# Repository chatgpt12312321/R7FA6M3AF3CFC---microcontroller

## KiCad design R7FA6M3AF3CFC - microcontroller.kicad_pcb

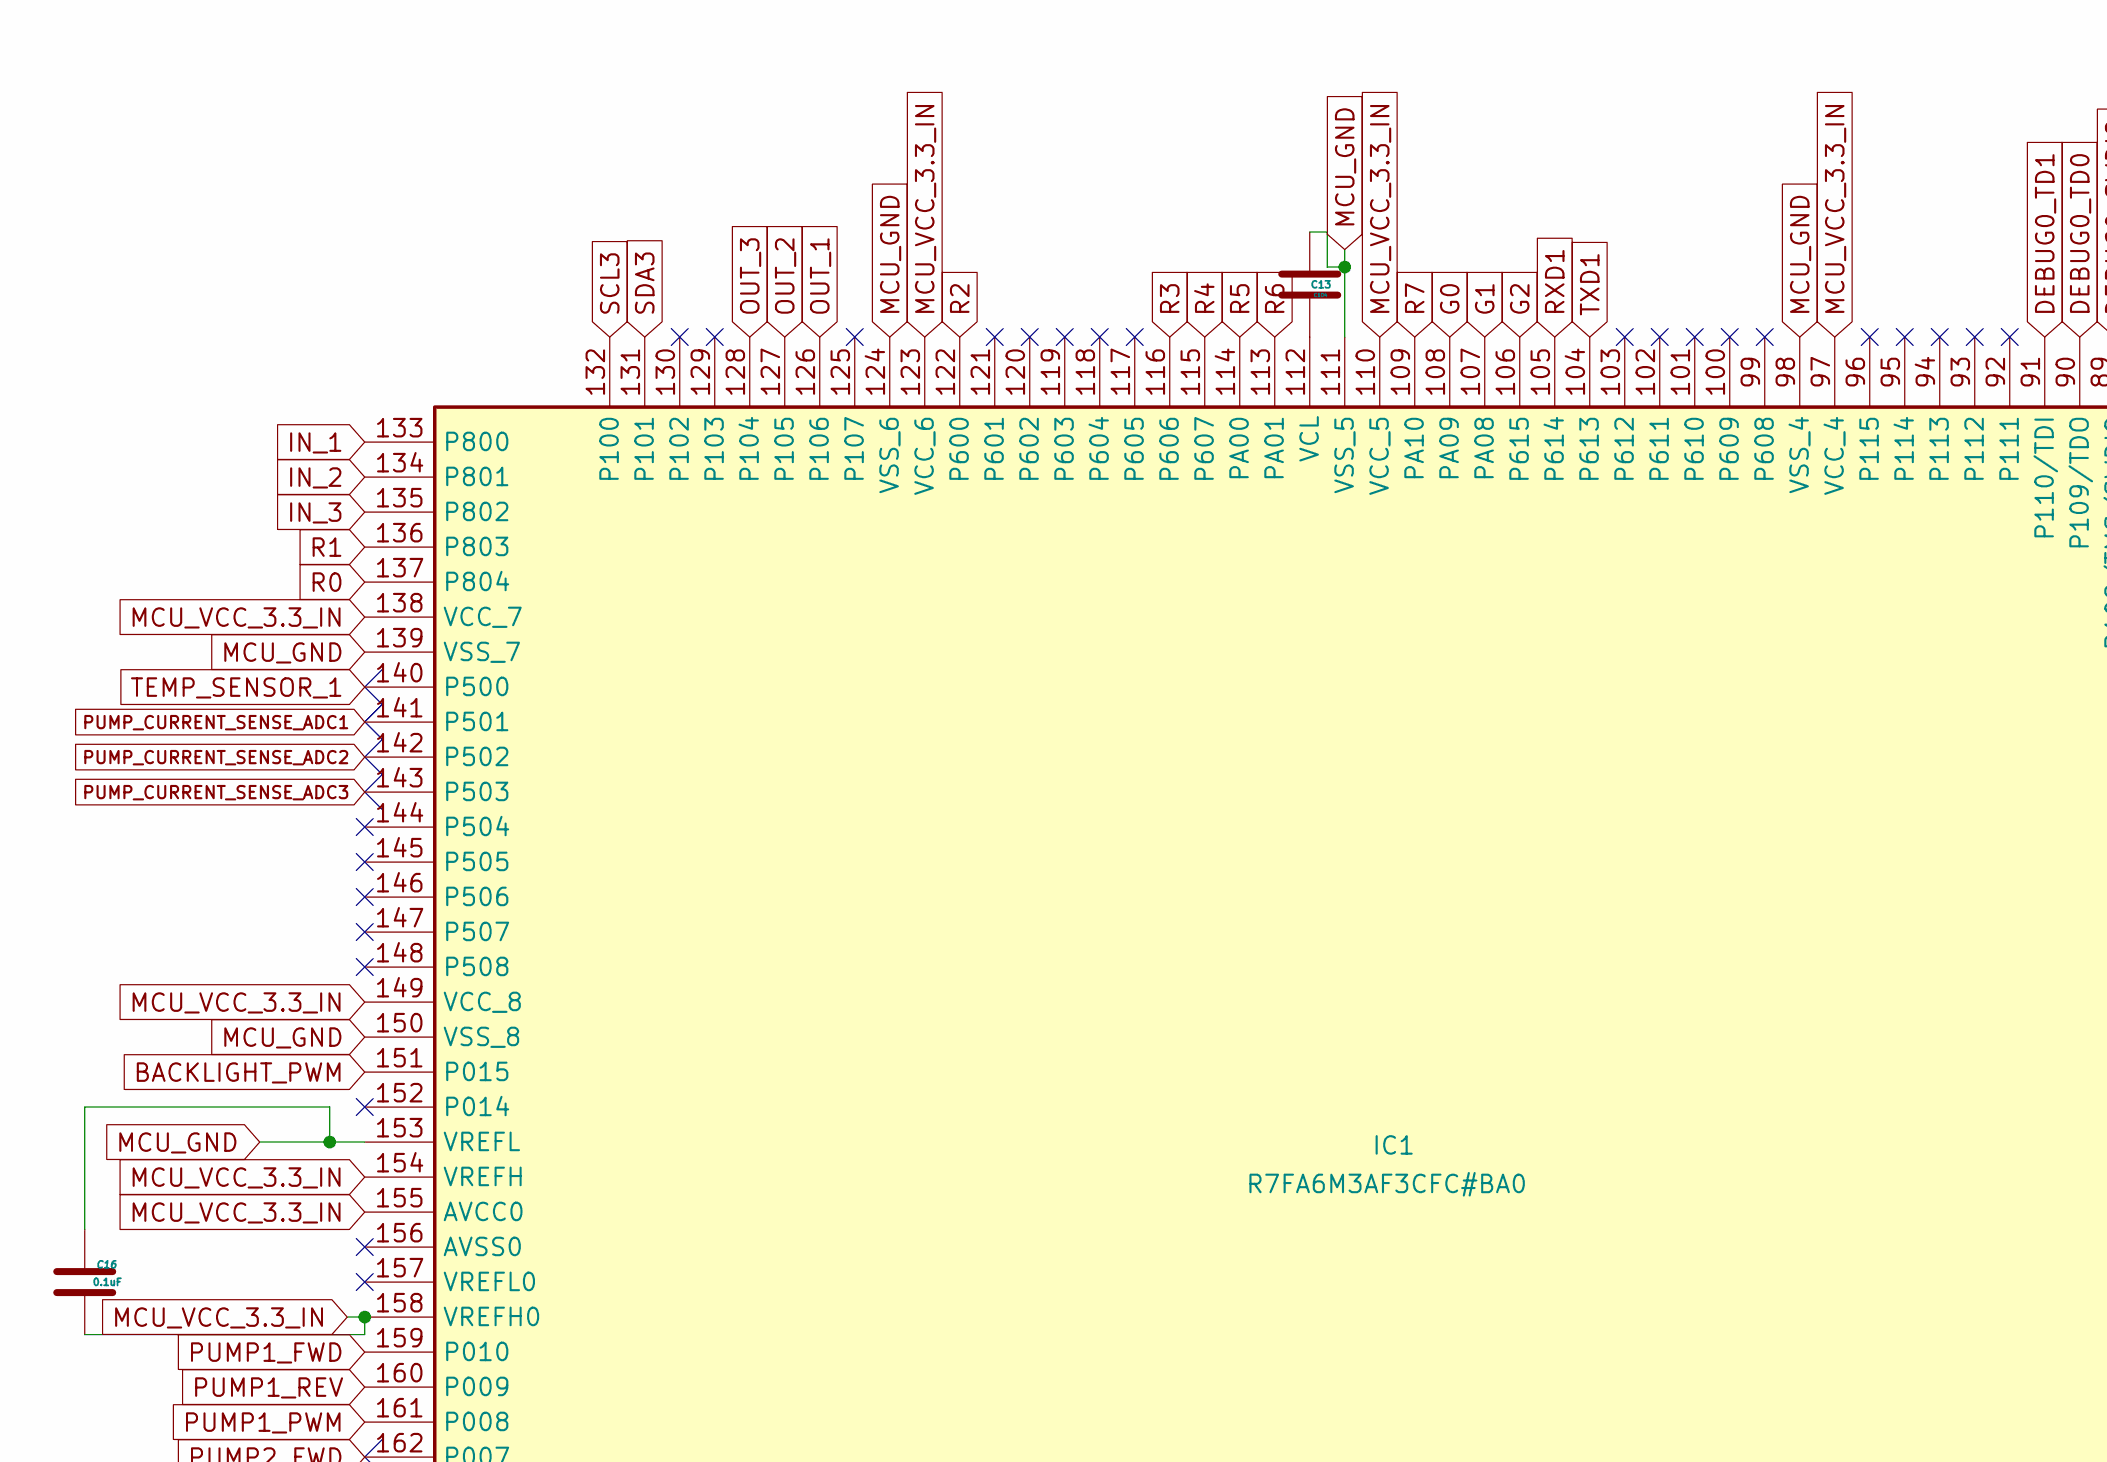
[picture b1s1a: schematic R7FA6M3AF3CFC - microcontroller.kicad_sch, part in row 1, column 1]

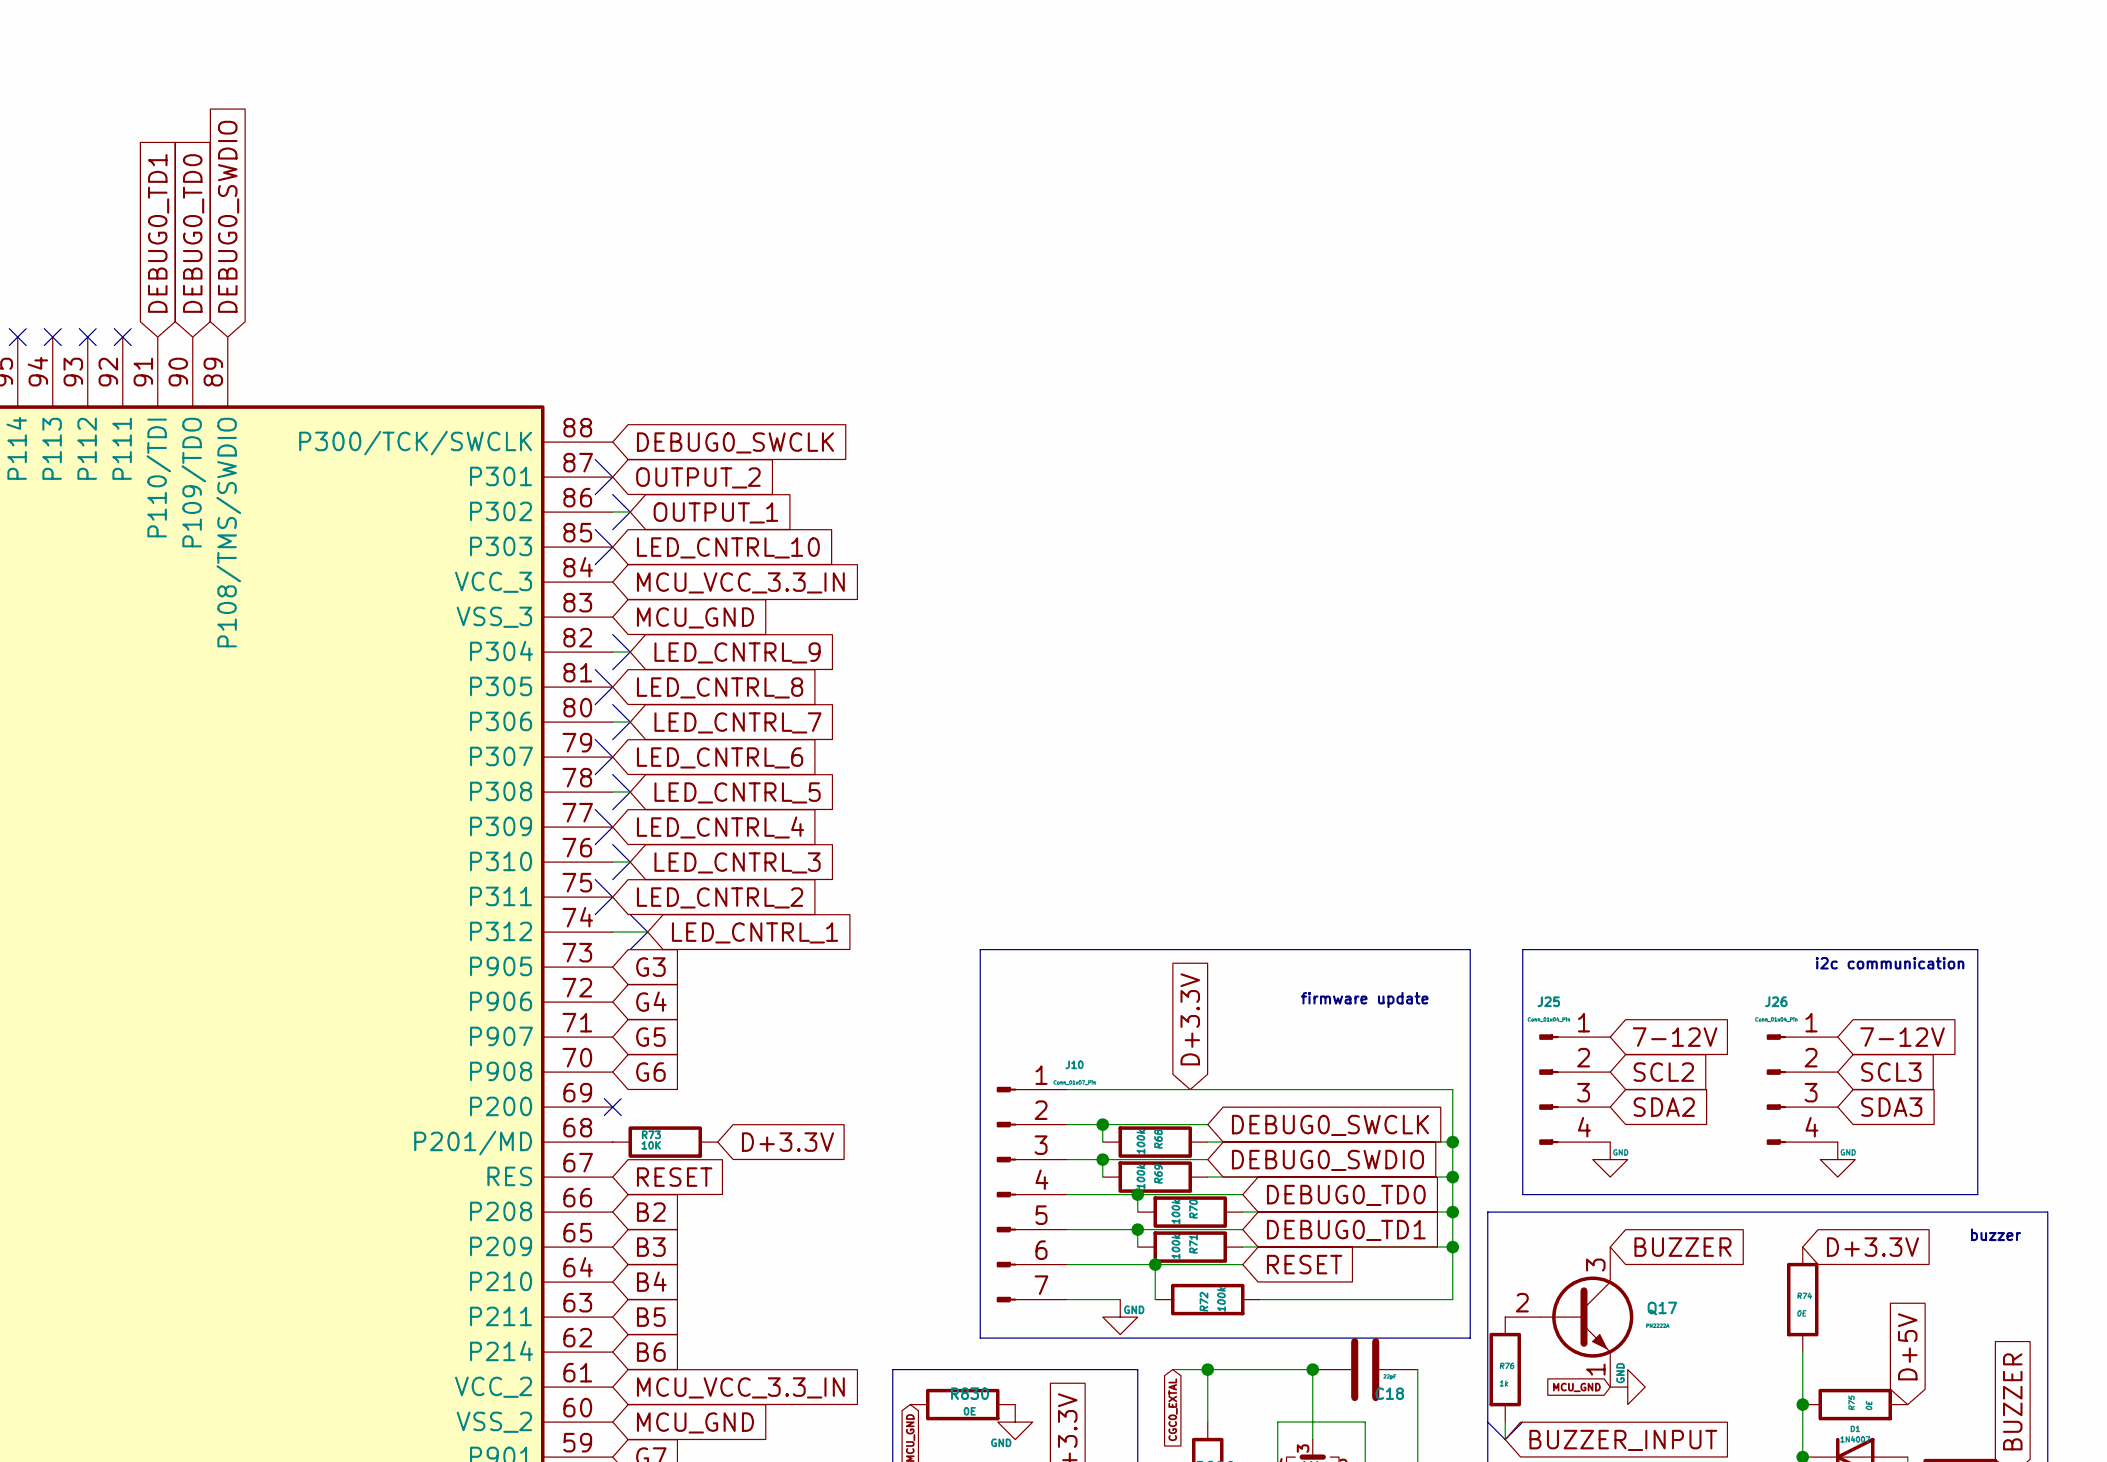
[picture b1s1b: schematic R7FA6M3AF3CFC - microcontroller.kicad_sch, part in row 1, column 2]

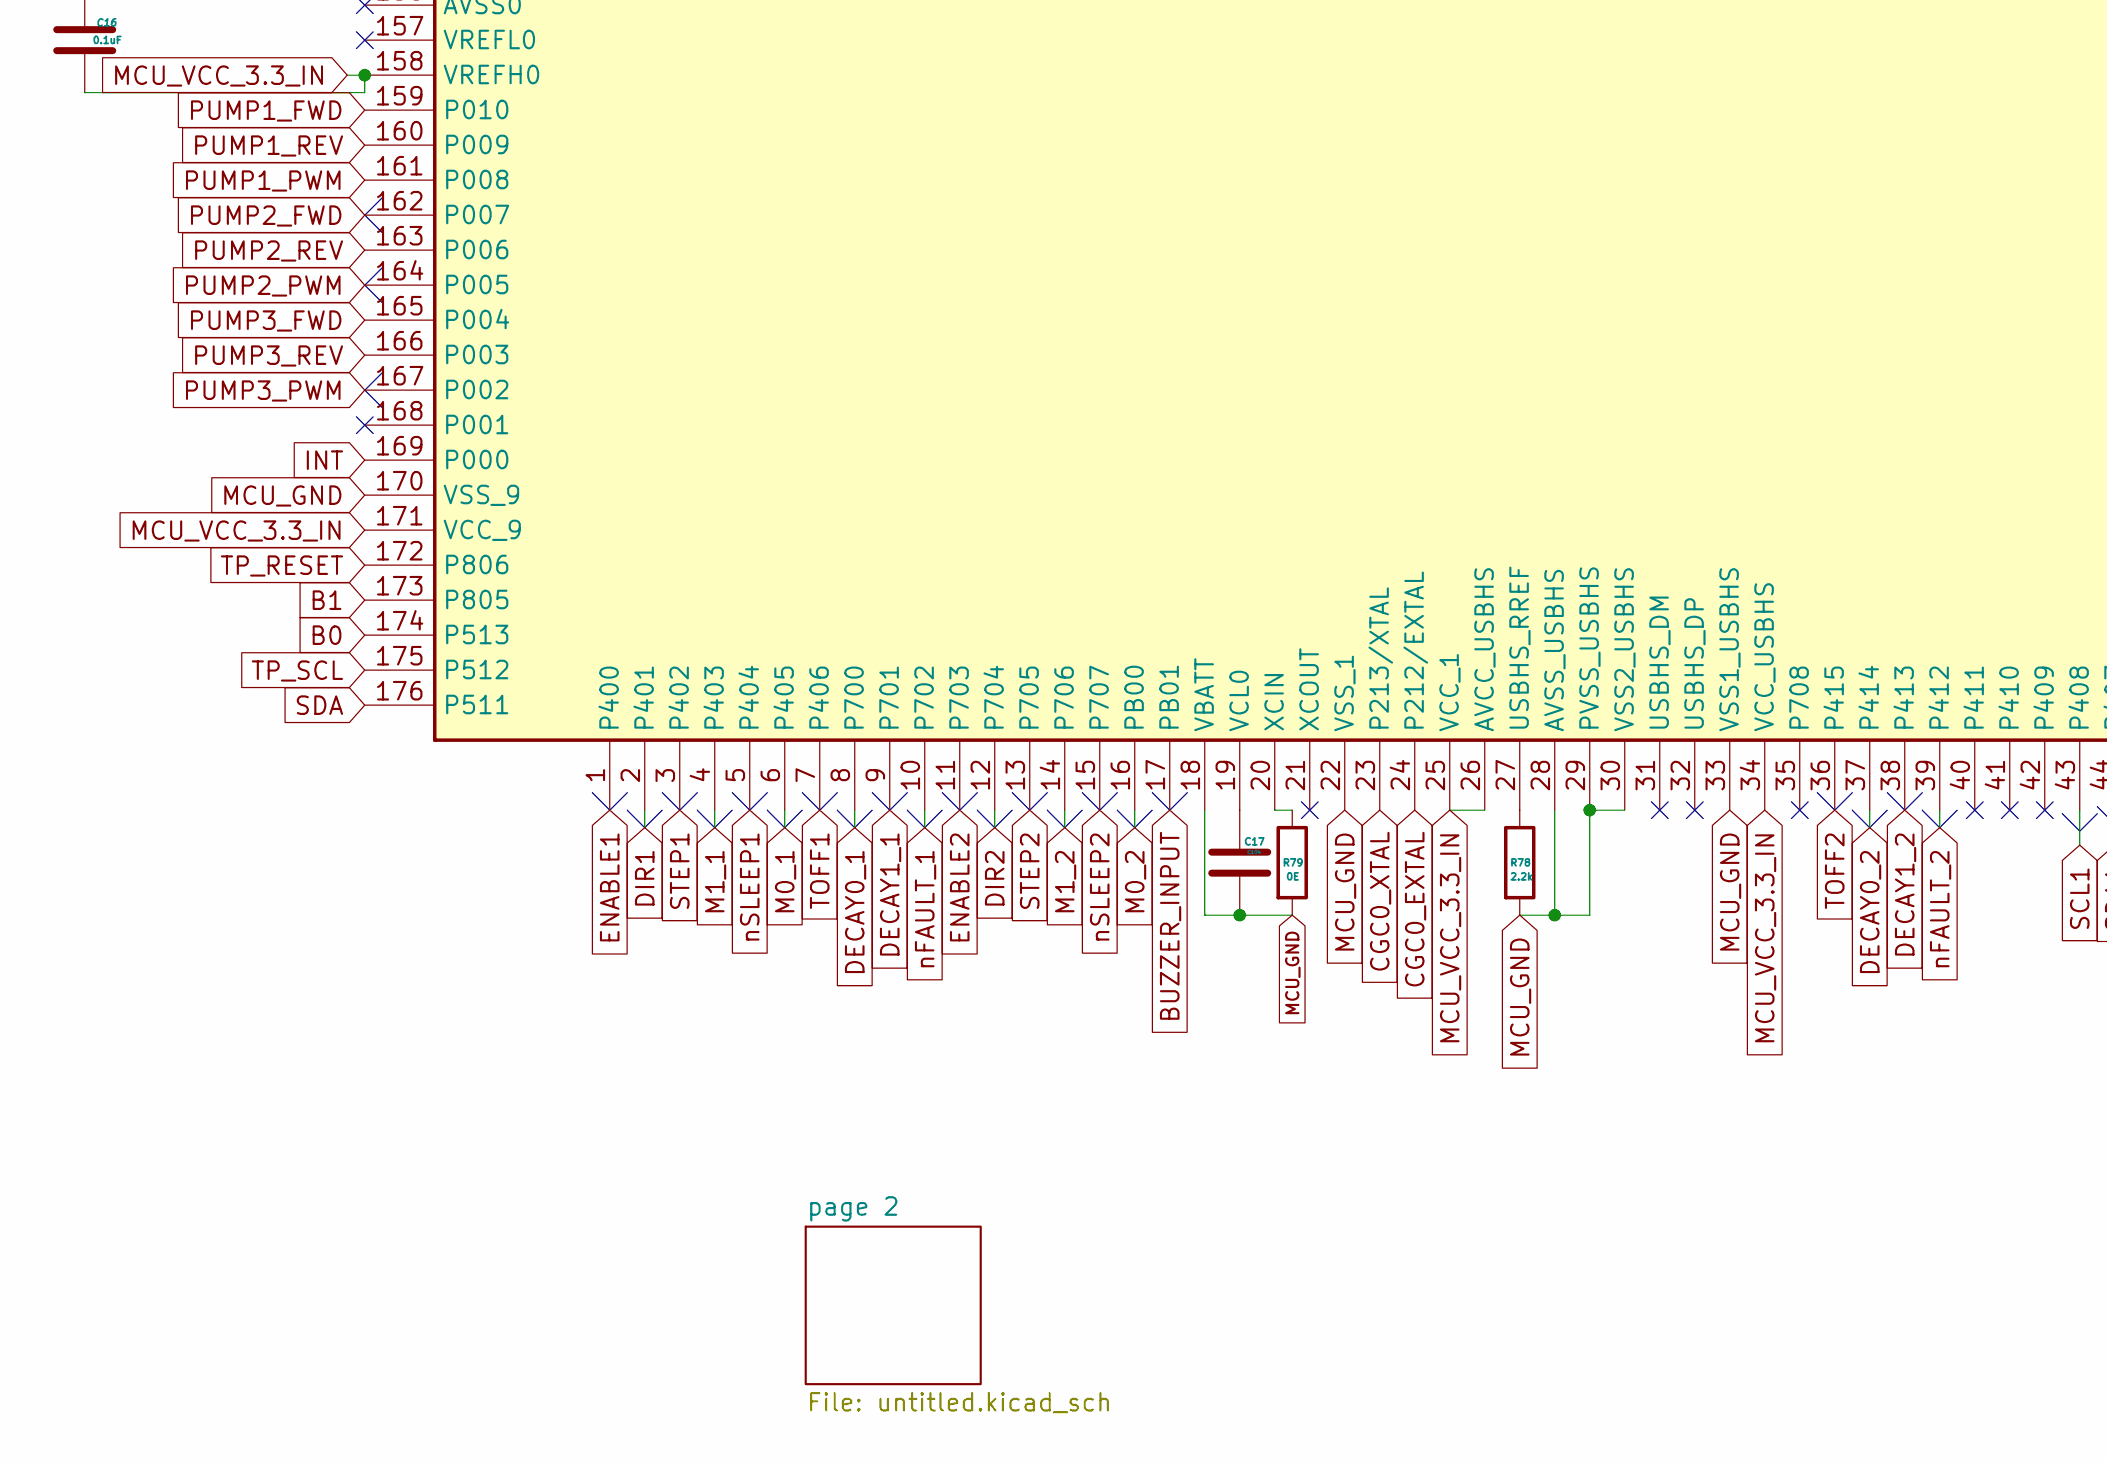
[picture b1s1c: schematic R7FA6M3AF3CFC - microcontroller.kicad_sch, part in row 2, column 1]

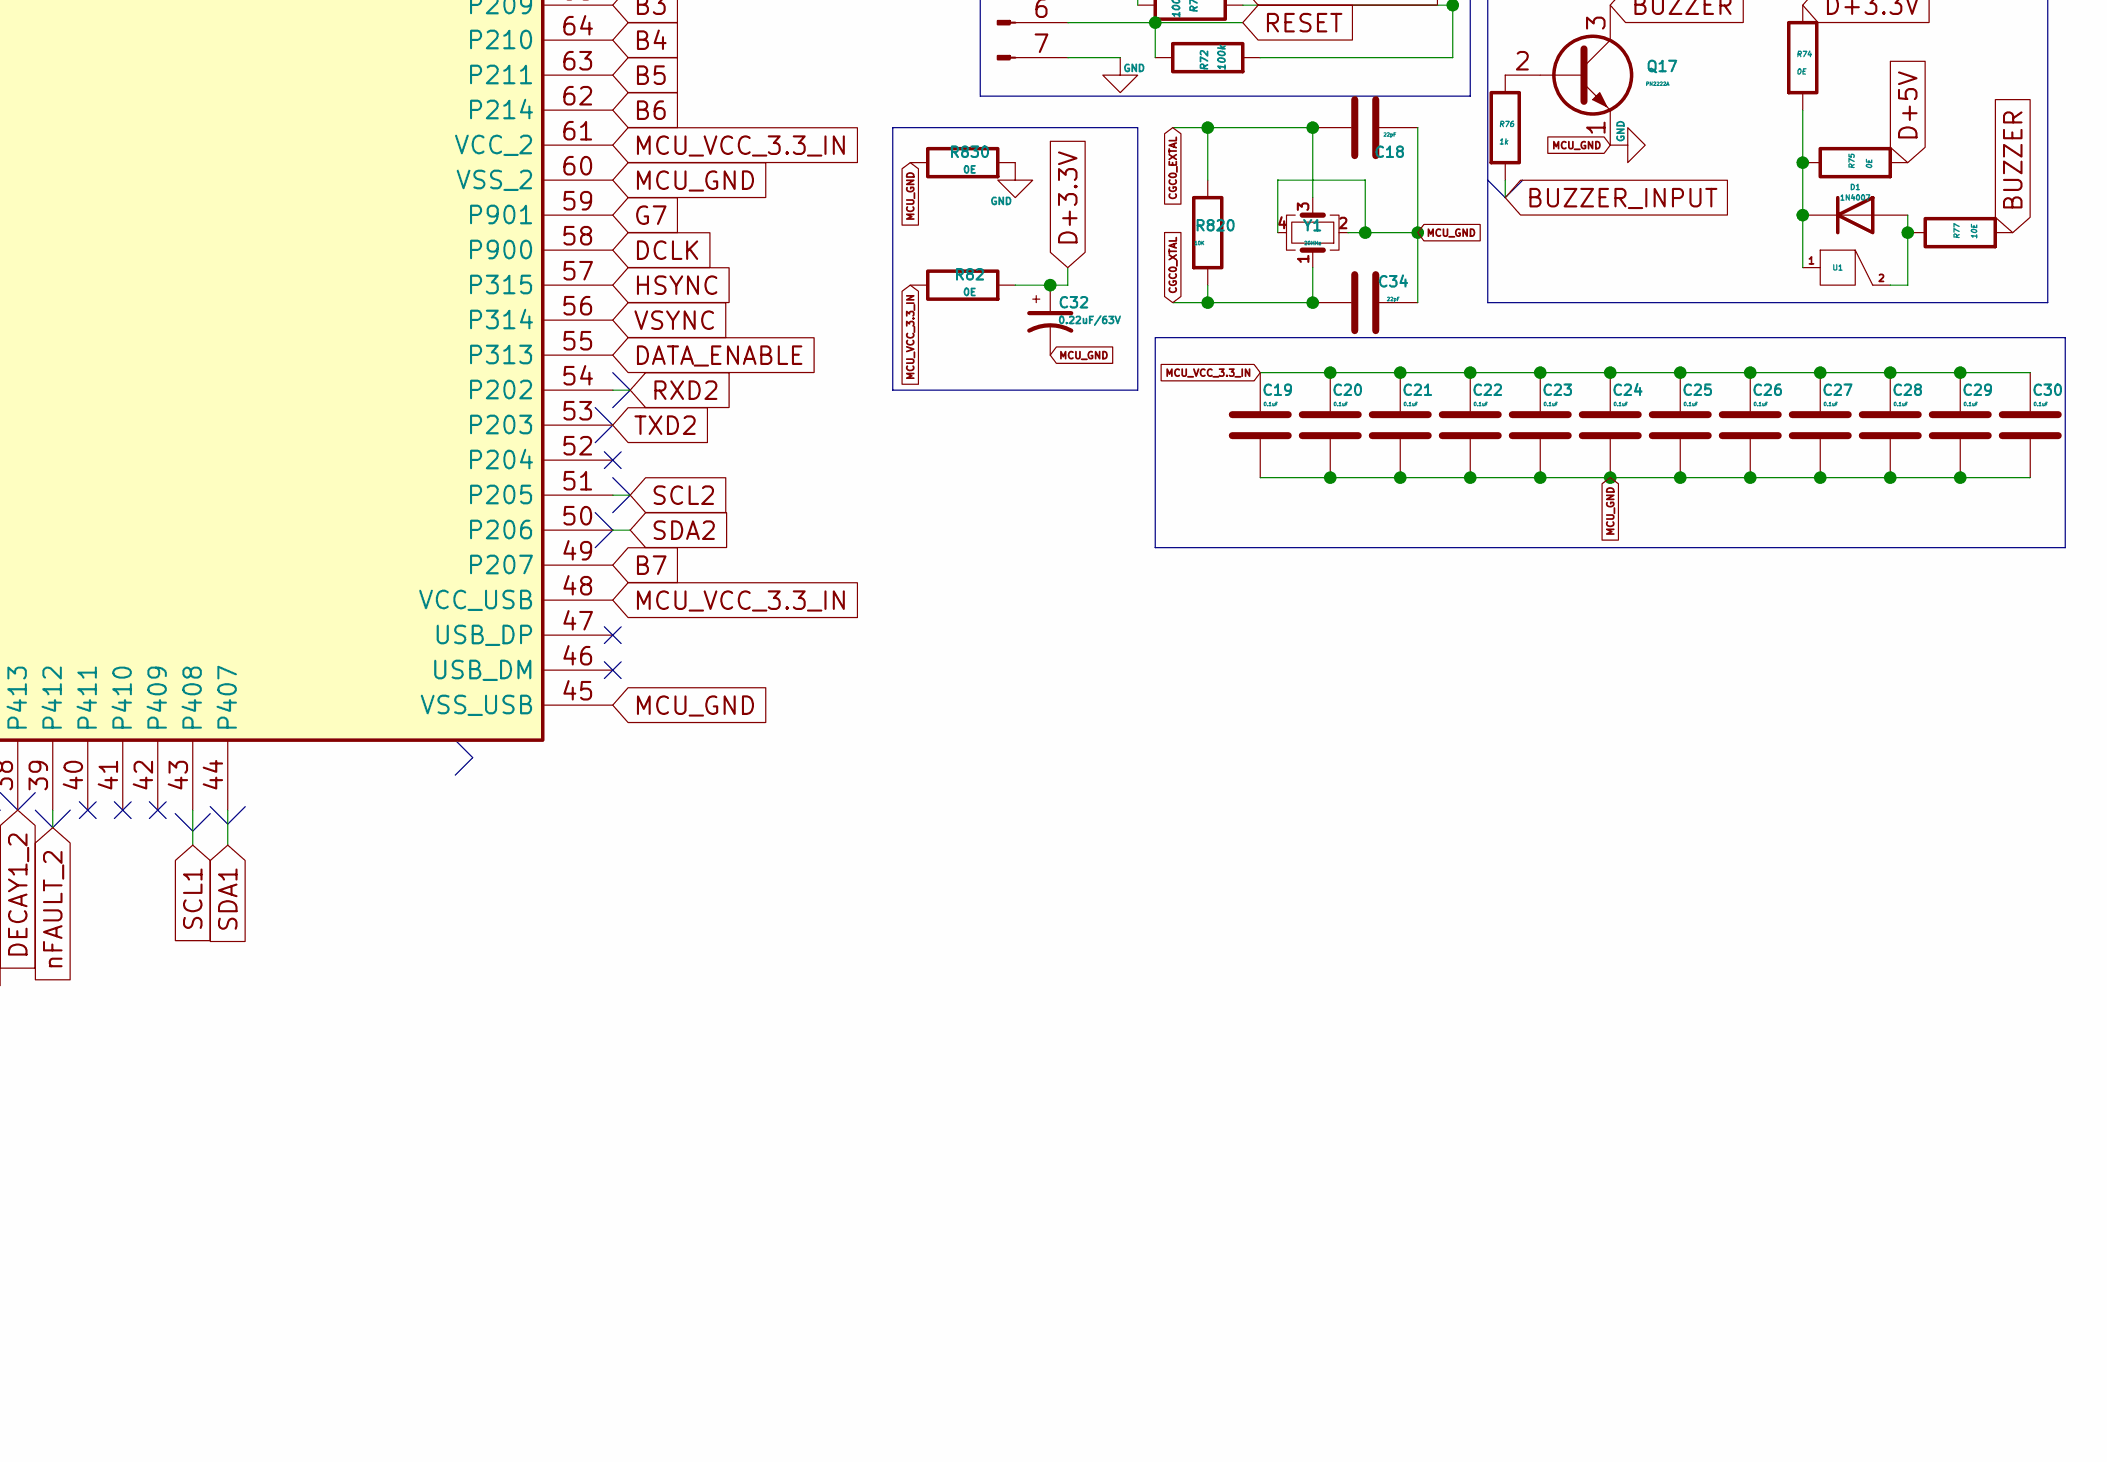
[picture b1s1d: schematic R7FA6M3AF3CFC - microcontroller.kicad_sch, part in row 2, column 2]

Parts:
C13, C17: C104; C_0402_1005Metric_Pad0.74x0.62mm_HandSolder
C16, C19, C20, C21, C22, C23, C24, C25, C26, C27, C28, C29, C30: 0.1uF; C_0402_1005Metric_Pad0.74x0.62mm_HandSolder
C18, C34: 22pF; C_0402_1005Metric_Pad0.74x0.62mm_HandSolder
C32: 0.22uF/63V; C_0402_1005Metric_Pad0.74x0.62mm_HandSolder
D1: 1N4007; D_DO-41_SOD81_P10.16mm_Horizontal
IC1: R7FA6M3AF3CFC#BA0; QFP50P2600X2600X170-176M; Manufacturer_Part_Number R7FA6M3AF3CFC#BA0
J10: Conn_01x07_Pin; PinHeader_1x07_P2.54mm_Vertical_SMD_Pin1Right
J25, J26: Conn_01x04_Pin; PinHeader_1x04_P2.54mm_Vertical_SMD_Pin1Right
Q17: PN2222A; TO-92_Inline
R68, R69, R70, R71, R72: 100k; R_0805_2012Metric_Pad1.20x1.40mm_HandSolder
R73, R820: 10K; R_0805_2012Metric_Pad1.20x1.40mm_HandSolder
R74, R75, R79, R82, R830: 0E; R_0805_2012Metric_Pad1.20x1.40mm_HandSolder
R76: 1k; R_0805_2012Metric_Pad1.20x1.40mm_HandSolder
R77: 10E; R_0805_2012Metric_Pad1.20x1.40mm_HandSolder
R78: 2.2k; R_0805_2012Metric_Pad1.20x1.40mm_HandSolder
U1: Buzzer_12x9.5RM7.6
Y1: 20MHz; Crystal_C38-LF_D3.0mm_L8.0mm_Vertical

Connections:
7-12V: J25.1, J26.1
B0: IC1.174 (P513); also elsewhere on the board
B1: IC1.173 (P805); also elsewhere on the board
B2: IC1.66 (P208); also elsewhere on the board
B3: IC1.65 (P209); also elsewhere on the board
B4: IC1.64 (P210); also elsewhere on the board
B5: IC1.63 (P211); also elsewhere on the board
B6: IC1.62 (P214); also elsewhere on the board
B7: IC1.49 (P207); also elsewhere on the board
BACKLIGHT_PWM: IC1.151 (P015); also elsewhere on the board
BUZZER: Q17.3 (C), R77.2
BUZZER_INPUT: IC1.17 (PB01), R76.2
CGC0_EXTAL: C18.2, IC1.24 (P212/EXTAL), R820.1, Y1.3
CGC0_XTAL: C34.1, IC1.23 (P213/XTAL), R820.2, Y1.1
D+3.3V: C32.1, J10.1, R68.1, R69.1, R70.1, R71.1, R72.2, R73.2, R74.1, R82.2; also elsewhere on the board
D+5V: R75.2; also elsewhere on the board
DATA_ENABLE: IC1.55 (P313); also elsewhere on the board
DCLK: IC1.58 (P900); also elsewhere on the board
DEBUG0_SWCLK: IC1.88 (P300/TCK/SWCLK), J10.2, R68.2
DEBUG0_SWDIO: IC1.89 (P108/TMS/SWDIO), J10.3, R69.2
DEBUG0_TD0: IC1.90 (P109/TDO), J10.4, R70.2
DEBUG0_TD1: IC1.91 (P110/TDI), J10.5, R71.2
DECAY0_1: IC1.8 (P700); also elsewhere on the board
DECAY0_2: IC1.37 (P414); also elsewhere on the board
DECAY1_1: IC1.9 (P701); also elsewhere on the board
DECAY1_2: IC1.38 (P413); also elsewhere on the board
DIR1: IC1.2 (P401); also elsewhere on the board
DIR2: IC1.12 (P704); also elsewhere on the board
ENABLE1: IC1.1 (P400); also elsewhere on the board
ENABLE2: IC1.11 (P703); also elsewhere on the board
G0: IC1.108 (PA09); also elsewhere on the board
G1: IC1.107 (PA08); also elsewhere on the board
G2: IC1.106 (P615); also elsewhere on the board
G3: IC1.73 (P905); also elsewhere on the board
G4: IC1.72 (P906); also elsewhere on the board
G5: IC1.71 (P907); also elsewhere on the board
G6: IC1.70 (P908); also elsewhere on the board
G7: IC1.59 (P901); also elsewhere on the board
HSYNC: IC1.57 (P315); also elsewhere on the board
INT: IC1.169 (P000); also elsewhere on the board
IN_1: IC1.133 (P800); also elsewhere on the board
IN_2: IC1.134 (P801); also elsewhere on the board
IN_3: IC1.135 (P802); also elsewhere on the board
LED_CNTRL_1: IC1.74 (P312); also elsewhere on the board
LED_CNTRL_2: IC1.75 (P311); also elsewhere on the board
LED_CNTRL_3: IC1.76 (P310); also elsewhere on the board
LED_CNTRL_4: IC1.77 (P309); also elsewhere on the board
LED_CNTRL_5: IC1.78 (P308); also elsewhere on the board
LED_CNTRL_6: IC1.79 (P307); also elsewhere on the board
LED_CNTRL_7: IC1.80 (P306); also elsewhere on the board
LED_CNTRL_8: IC1.81 (P305); also elsewhere on the board
LED_CNTRL_9: IC1.82 (P304); also elsewhere on the board
LED_CNTRL_10: IC1.85 (P303); also elsewhere on the board
M0_1: IC1.6 (P405); also elsewhere on the board
M0_2: IC1.16 (PB00); also elsewhere on the board
M1_1: IC1.4 (P403); also elsewhere on the board
M1_2: IC1.14 (P706); also elsewhere on the board
MCU_GND: C13.1, C16.1, C17.2, C18.1, C19.2, C20.2, C21.2, C22.2, C23.2, C24.2, C25.2, C26.2, C27.2, C28.2, C29.2, C30.2, C32.2, C34.2, IC1.18 (VBATT), IC1.22 (VSS_1), IC1.28 (AVSS_USBHS), IC1.29 (PVSS_USBHS), IC1.30 (VSS2_USBHS), IC1.33 (VSS1_USBHS), IC1.45 (VSS_USB), IC1.60 (VSS_2), IC1.83 (VSS_3), IC1.98 (VSS_4), IC1.111 (VSS_5), IC1.124 (VSS_6), IC1.139 (VSS_7), IC1.150 (VSS_8), IC1.153 (VREFL), IC1.170 (VSS_9), J10.7, J25.4, J26.4, Q17.1 (E), R78.2, R79.2, R830.1, R830.2, Y1.2, Y1.4; also elsewhere on the board
MCU_VCC_3.3_IN: C16.2, C19.1, C20.1, C21.1, C22.1, C23.1, C24.1, C25.1, C26.1, C27.1, C28.1, C29.1, C30.1, IC1.25 (VCC_1), IC1.26 (AVCC_USBHS), IC1.34 (VCC_USBHS), IC1.48 (VCC_USB), IC1.61 (VCC_2), IC1.84 (VCC_3), IC1.97 (VCC_4), IC1.110 (VCC_5), IC1.123 (VCC_6), IC1.138 (VCC_7), IC1.149 (VCC_8), IC1.154 (VREFH), IC1.155 (AVCC0), IC1.158 (VREFH0), IC1.171 (VCC_9), R82.1
unnamed: D1.2 (A), R77.1, U1.2
unnamed: D1.1 (K), R74.2, R75.1, U1.1
unnamed: IC1.68 (P201/MD), R73.1
unnamed: IC1.27 (USBHS_RREF), R78.1
unnamed: C17.1, IC1.19 (VCL0)
unnamed: C13.2, IC1.112 (VCL)
unnamed: IC1.20 (XCIN), R79.1
unnamed: Q17.2 (B), R76.1
OUTPUT_1: IC1.86 (P302); also elsewhere on the board
OUTPUT_2: IC1.87 (P301); also elsewhere on the board
OUT_1: IC1.126 (P106)
OUT_2: IC1.127 (P105)
OUT_3: IC1.128 (P104)
PUMP1_FWD: IC1.159 (P010); also elsewhere on the board
PUMP1_PWM: IC1.161 (P008); also elsewhere on the board
PUMP1_REV: IC1.160 (P009); also elsewhere on the board
PUMP2_FWD: IC1.162 (P007); also elsewhere on the board
PUMP2_PWM: IC1.164 (P005); also elsewhere on the board
PUMP2_REV: IC1.163 (P006); also elsewhere on the board
PUMP3_FWD: IC1.165 (P004); also elsewhere on the board
PUMP3_PWM: IC1.167 (P002); also elsewhere on the board
PUMP3_REV: IC1.166 (P003); also elsewhere on the board
PUMP_CURRENT_SENSE_ADC1: IC1.141 (P501); also elsewhere on the board
PUMP_CURRENT_SENSE_ADC2: IC1.142 (P502); also elsewhere on the board
PUMP_CURRENT_SENSE_ADC3: IC1.143 (P503); also elsewhere on the board
R0: IC1.137 (P804); also elsewhere on the board
R1: IC1.136 (P803); also elsewhere on the board
R2: IC1.122 (P600); also elsewhere on the board
R3: IC1.116 (P606); also elsewhere on the board
R4: IC1.115 (P607); also elsewhere on the board
R5: IC1.114 (PA00); also elsewhere on the board
R6: IC1.113 (PA01); also elsewhere on the board
R7: IC1.109 (PA10); also elsewhere on the board
RESET: IC1.67 (RES), J10.6, R72.1
RXD1: IC1.105 (P614); also elsewhere on the board
RXD2: IC1.54 (P202); also elsewhere on the board
SCL1: IC1.43 (P408); also elsewhere on the board
SCL2: IC1.51 (P205), J25.2
SCL3: IC1.132 (P100), J26.2
SDA: IC1.176 (P511)
SDA1: IC1.44 (P407); also elsewhere on the board
SDA2: IC1.50 (P206), J25.3
SDA3: IC1.131 (P101), J26.3
STEP1: IC1.3 (P402); also elsewhere on the board
STEP2: IC1.13 (P705); also elsewhere on the board
TEMP_SENSOR_1: IC1.140 (P500); also elsewhere on the board
TOFF1: IC1.7 (P406); also elsewhere on the board
TOFF2: IC1.36 (P415); also elsewhere on the board
TP_RESET: IC1.172 (P806); also elsewhere on the board
TP_SCL: IC1.175 (P512); also elsewhere on the board
TXD1: IC1.104 (P613); also elsewhere on the board
TXD2: IC1.53 (P203); also elsewhere on the board
VSYNC: IC1.56 (P314); also elsewhere on the board
nFAULT_1: IC1.10 (P702); also elsewhere on the board
nFAULT_2: IC1.39 (P412); also elsewhere on the board
nSLEEP1: IC1.5 (P404); also elsewhere on the board
nSLEEP2: IC1.15 (P707); also elsewhere on the board

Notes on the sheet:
buzzer
firmware update
i2c communication
